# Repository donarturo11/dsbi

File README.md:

# dsbi
(Damn Simple Brainwave Interface)

This is simple and modular interface for EEG acquisition.
Analog part is brought from [BioAmpExg](https://github.com/upsidedownlabs/BioAmp-EXG-Pill).
The goal of this project is easy assemblation by everyone with very small experience in electronics.
Circuit was tested with ESP32 and AVR Attiny13.

# Data format
Data are sent as raw unsigned 12-bit integer wave with sample rate 512 Hz in following format:
```
unsigned short meteredValue = HHHH HHLL LLLL
unsigned char firstByte  = 10HH HHHH # ( 0x80 | ( (meteredValue >> 6) & 0x3F) )
unsigned char secondByte = 01LL LLLL # ( 0x40 |   (meteredValue & 0x3F) )
```
# Specs
## Common:
* Interface: UART
* Sample rate 512 Hz
* Raw wave 12-bit unsigned short
## ESP32
* Sampling in 12-bit without oversampling
* Hardware UART 8-N-1
* Baudrate: 38400
## Attiny13
* Sampling in 10 bit with oversampling
* Software UART 8-N-2
* Baudrate: 19200
# Compatible software
* [QBrainwaveOSC](https://github.com/donarturo11/QBrainwaveOSC)

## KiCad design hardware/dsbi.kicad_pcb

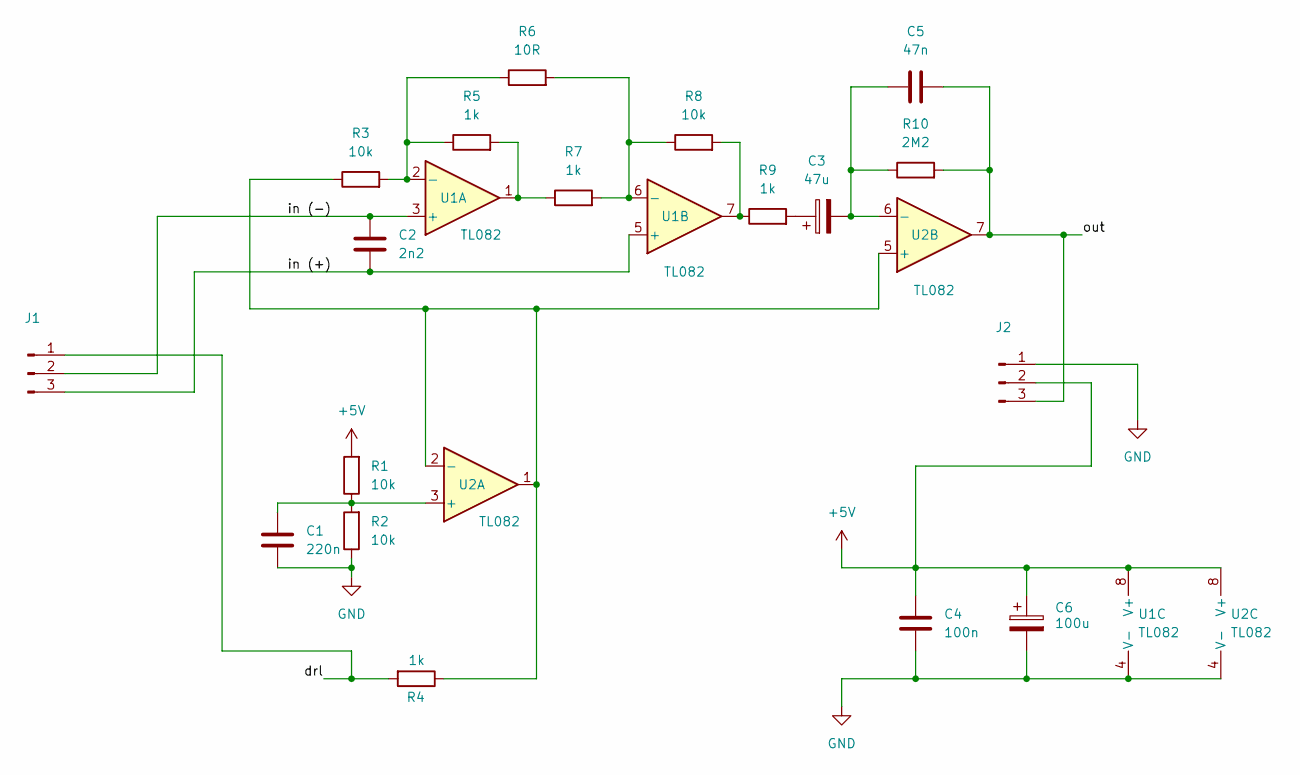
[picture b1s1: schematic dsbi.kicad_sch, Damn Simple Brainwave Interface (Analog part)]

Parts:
C1: 220n; C_Disc_D3.0mm_W1.6mm_P2.50mm
C2: 2n2; C_Disc_D3.0mm_W1.6mm_P2.50mm
C3: 47u; CP_Radial_D8.0mm_P5.00mm
C4: 100n; C_Disc_D3.0mm_W1.6mm_P2.50mm
C5: 47n; C_Disc_D3.0mm_W1.6mm_P2.50mm
C6: 100u; CP_Radial_D8.0mm_P5.00mm
J1, J2: FanPinHeader_1x03_P2.54mm_Vertical
R1, R2, R3, R8: 10k; R_Axial_DIN0207_L6.3mm_D2.5mm_P10.16mm_Horizontal
R4, R5, R7, R9: 1k; R_Axial_DIN0207_L6.3mm_D2.5mm_P10.16mm_Horizontal
R6: 10R; R_Axial_DIN0207_L6.3mm_D2.5mm_P10.16mm_Horizontal
R10: 2M2; R_Axial_DIN0207_L6.3mm_D2.5mm_P10.16mm_Horizontal
U1, U2: TL082; DIP-8_W7.62mm_Socket

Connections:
+5V: C4.2, C6.1, J2.2, R1.2, U1.8 (V+), U2.8 (V+)
/drl: J1.1, R4.2
/in (+): C2.2, J1.3, U1.5 (+)
/in (-): C2.1, J1.2, U1.3 (+)
/out: C5.2, J2.3, R10.2, U2.7
GND: C1.1, C4.1, C6.2, J2.1, R2.1, U1.4 (V-), U2.4 (V-)
unnamed: C3.1, R9.2
unnamed: R5.2, R7.1, U1.1
unnamed: R8.2, R9.1, U1.7
unnamed: R3.2, R5.1, R6.1, U1.2 (-)
unnamed: R6.2, R7.2, R8.1, U1.6 (-)
unnamed: C1.2, R1.1, R2.2, U2.3 (+)
unnamed: R3.1, R4.1, U2.1, U2.2 (-), U2.5 (+)
unnamed: C3.2, C5.1, R10.1, U2.6 (-)

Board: 2 copper layers, 20 parts (0 on the bottom side), 14 nets, no tracks yet.

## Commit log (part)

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2023-09-17 Some infos
2023-09-17 Add KiCad project
2023-09-17 Ignore backups
2023-09-17 Remove unecessary backups
2023-09-17 Add code for ESP32
2023-09-17 Add more informations about project and software
2023-09-18 Arrangement of elements
2023-09-18 paths
2023-09-19 Do not track production files
2023-09-19 Most paths
2023-09-19 Rearrange elements
2023-09-20 Create new PCB paths
2023-09-20 Add footprints
2023-09-20 Create ESP32 adapter
2023-09-20 Add custom footprints (lib)
2023-09-20 Finish analog part
2023-09-20 Initial create circuits (#1)
    * Arrangement of elements
    * paths
    * Do not track production files
    * Most paths
    * Rearrange elements
    * Create new PCB paths
2023-09-22 Improvements
2023-09-22 fix details
2023-09-22 Move text from back cu to front silkscreen
2023-09-23 Add documentation
2023-09-23 Modifications
2023-09-23 Add sheet to thermotransfer
2023-10-09 Connect TL072 ICs to GND
2023-10-09 Resize holes
2023-10-09 Resize holes #2
2023-10-09 Increase path distances
2023-12-23 Move code for ESP32 to another directory
2023-12-23 Initial commit firmware for attiny13
2023-12-23 Add README for ESP32 firmware
2023-12-28 Prepare circuit for test samplerate
2023-12-28 Add ADC oversampling, move sampling to interrupt
2024-01-03 Rewrite sampling, move soft TX to interrupt, prepare queue
2024-01-22 Fix missing ground connection for ground for opamps
2024-01-22 Fix paths, improve distances
2024-01-22 Allow for add PDF
2024-01-22 Add PDFs for easily printing
2024-04-02 Reorganize main
2024-04-02 Set simulator's baudrate from 33400 to 38400
2024-04-02 Modularize code for adc
2024-04-02 Primitive implementation of FIFO buffer
2024-04-02 Add objects: fifo, adc
2024-04-03 Prevent tracking result files created after build
2024-04-03 Remove unecessary build options
2024-04-10 Change ESP32 firmware to unsigned 2-byte raw wave
2024-04-10 Sine wave as test
2024-04-10 Rewrite data transmission, improvements to metering
2024-04-11 Lower test frequency
2024-04-11 Clean code, improve ADC metering
2024-04-11 Move transmission to another file
2024-04-11 Improvements for makefile
2024-04-11 Add connections description
2024-04-13 Backup experimental codes
2024-04-13 Update simulator file
2024-04-13 Simplify TX transmission
2024-04-13 Rewrite adc sampling
2024-04-13 Rewrite and simplify code
2024-04-23 Update README according to changes inside firmwares
2024-06-17 Update compatible software list
2024-07-25 Rename sketch file for ESP32
2024-07-25 Add sketch for Arduino
2024-09-08 Make code more universal for several microcontrollers
2024-09-08 Add more instructions for another microcontrollers for use in Arduino IDE
2024-09-08 Remove unnecessary sketch because using universal one for Arduino
2026-02-19 Add improved version of firmware for attiny
2026-03-28 Reorganize sources
2026-03-28 Add schematics and simulide simulations
2026-03-28 Enable possibility of compiling with debug
2026-03-31 Save simulation in output directory
2026-03-31 Tidy code
2026-03-31 Improve ignoring production garbages
2026-04-03 Make simulation slower and add logic analyser
2026-04-03 Prevent tracking vim session files
2026-04-08 Implement optional averaging
